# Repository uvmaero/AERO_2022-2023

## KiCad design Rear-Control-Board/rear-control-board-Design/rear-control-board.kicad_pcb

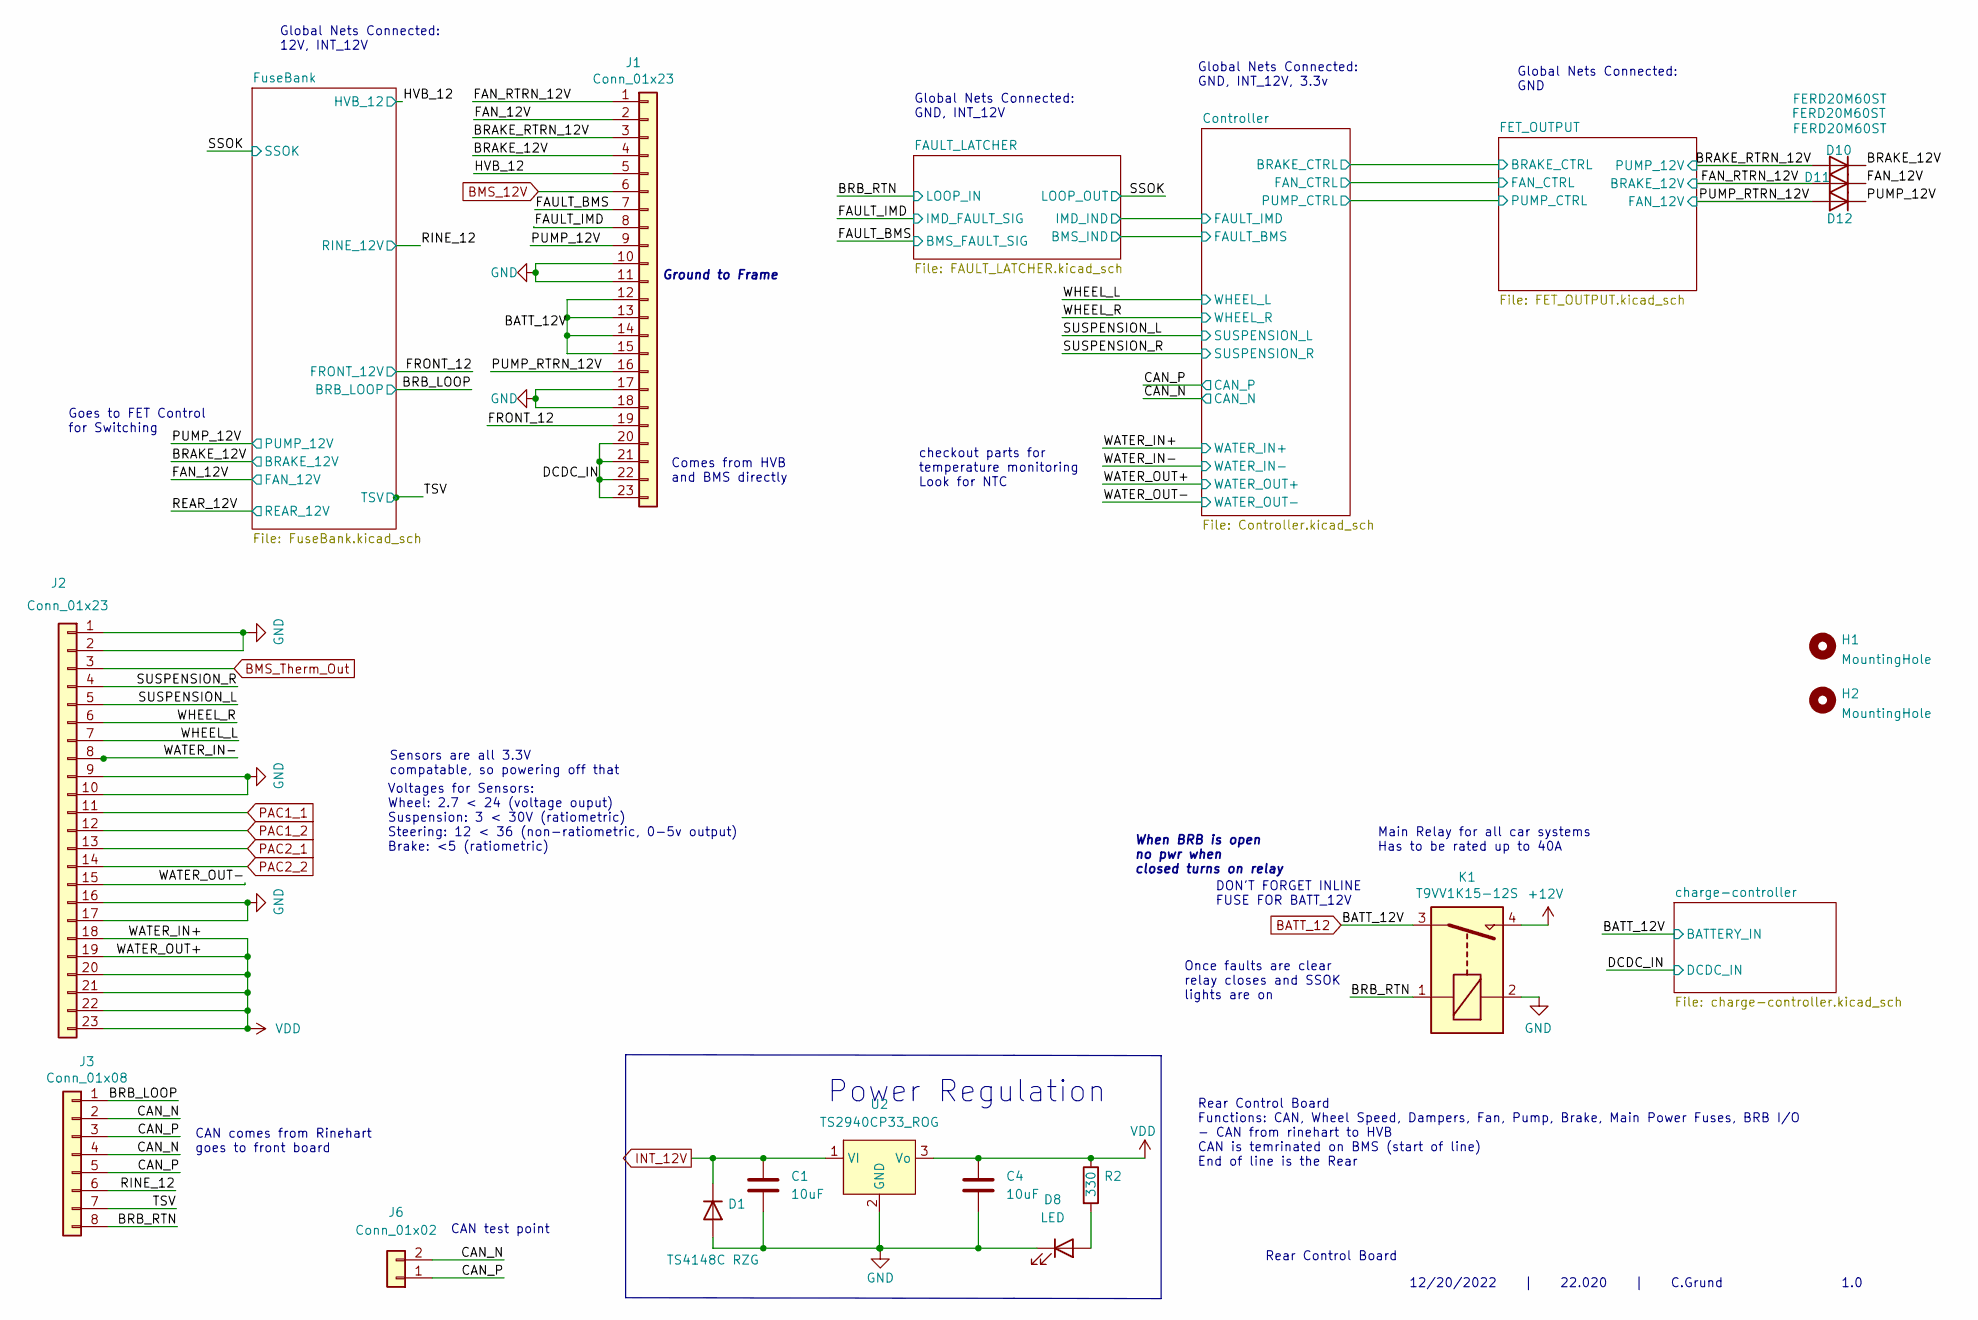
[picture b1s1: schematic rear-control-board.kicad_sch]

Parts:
C1, C4: 10uF; C_0603_1608Metric_Pad1.08x0.95mm_HandSolder
D1: TS4148C RZG; D_0603_1608Metric_Pad1.05x0.95mm_HandSolder
D8: LED; LED_0603_1608Metric_Pad1.05x0.95mm_HandSolder
D10, D11, D12: FERD20M60ST; TO-220-3_Vertical
H1, H2: MountingHole; MountingHole_3.2mm_M3
J1, J2: Conn_01x23; TE_1-770669-1_23pin_Horizontal
J3: Conn_01x08; TE_1-776280-1_8pin_Horizontal
J6: Conn_01x02; JST_NV_B02P-NV_1x02_P5.00mm_Vertical
K1: T9VV1K15-12S; RELAY_T9VV1K15-12S
R2: 330; R_0603_1608Metric_Pad0.98x0.95mm_HandSolder
U2: TS2940CP33_ROG; TO-252-2

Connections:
+12V: K1.4; also elsewhere on the board
/BRAKE_12V: D10.2 (K), J1.4; also elsewhere on the board
/BRAKE_RTRN_12V: D10.1 (A), J1.3; also elsewhere on the board
/BRB_LOOP: J3.1; also elsewhere on the board
/CAN_N: J3.2, J3.4, J6.2; also elsewhere on the board
/CAN_P: J3.3, J3.5, J6.1; also elsewhere on the board
/DCDC_IN: J1.20, J1.21, J1.22, J1.23; also elsewhere on the board
/FAN_12V: D11.2 (K), J1.2; also elsewhere on the board
/FAN_RTRN_12V: D11.1 (A), J1.1; also elsewhere on the board
/FAULT_IMD: J1.8; also elsewhere on the board
/FRONT_12: J1.19; also elsewhere on the board
/HVB_12: J1.5; also elsewhere on the board
/PUMP_12V: D12.2 (K), J1.9; also elsewhere on the board
/PUMP_RTRN_12V: D12.1 (A), J1.16; also elsewhere on the board
/RINE_12: J3.6; also elsewhere on the board
/SUSPENSION_L: J2.5; also elsewhere on the board
/SUSPENSION_R: J2.4; also elsewhere on the board
/TSV: J3.7; also elsewhere on the board
/WATER_IN-: J2.8; also elsewhere on the board
/WATER_OUT-: J2.15; also elsewhere on the board
/WHEEL_L: J2.7; also elsewhere on the board
/WHEEL_R: J2.6; also elsewhere on the board
BATT_12: J1.12, J1.13, J1.14, J1.15, K1.3; also elsewhere on the board
BMS_12V: J1.6; also elsewhere on the board
BMS_Therm_Out: J2.3; also elsewhere on the board
unnamed: D8.2 (A), R2.2
PAC1_1: J2.11; also elsewhere on the board
PAC1_2: J2.12; also elsewhere on the board
PAC2_1: J2.13; also elsewhere on the board
PAC2_2: J2.14; also elsewhere on the board
VDD: C4.1, J2.18, J2.19, J2.20, J2.21, J2.22, J2.23, R2.1, U2.3 (Vo); also elsewhere on the board

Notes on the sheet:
Once faults are clear relay closes and SSOK lights are on
1.0
Comes from HVB and BMS directly
Global Nets Connected: GND
Main Relay for all car systems Has to be rated up to 40A
checkout parts for temperature monitoring Look for NTC
When BRB is open no pwr when closed turns on relay
Global Nets Connected: GND, INT_12V
Voltages for Sensors: Wheel: 2.7 < 24 (voltage ouput) Suspension: 3 < 30V (ratiometric) Steering: 12 < 36 (non-ratiometric, 0-5v output) Brake: <5 (ratiometric)
DON'T FORGET INLINE FUSE FOR BATT_12V
CAN test point
12/20/2022 | 22.020 | C.Grund
Rear Control Board Functions: CAN, Wheel Speed, Dampers, Fan, Pump, Brake, Main Power Fuses, BRB I/O - CAN from rinehart to HVB CAN is temrinated on BMS (start of line) End of line is the Rear
Goes to FET Control for Switching
Ground to Frame
CAN comes from Rinehart goes to front board
Power Regulation
Global Nets Connected: GND, INT_12V, 3.3v
Sensors are all 3.3V compatable, so powering off that
Global Nets Connected: 12V, INT_12V
Rear Control Board

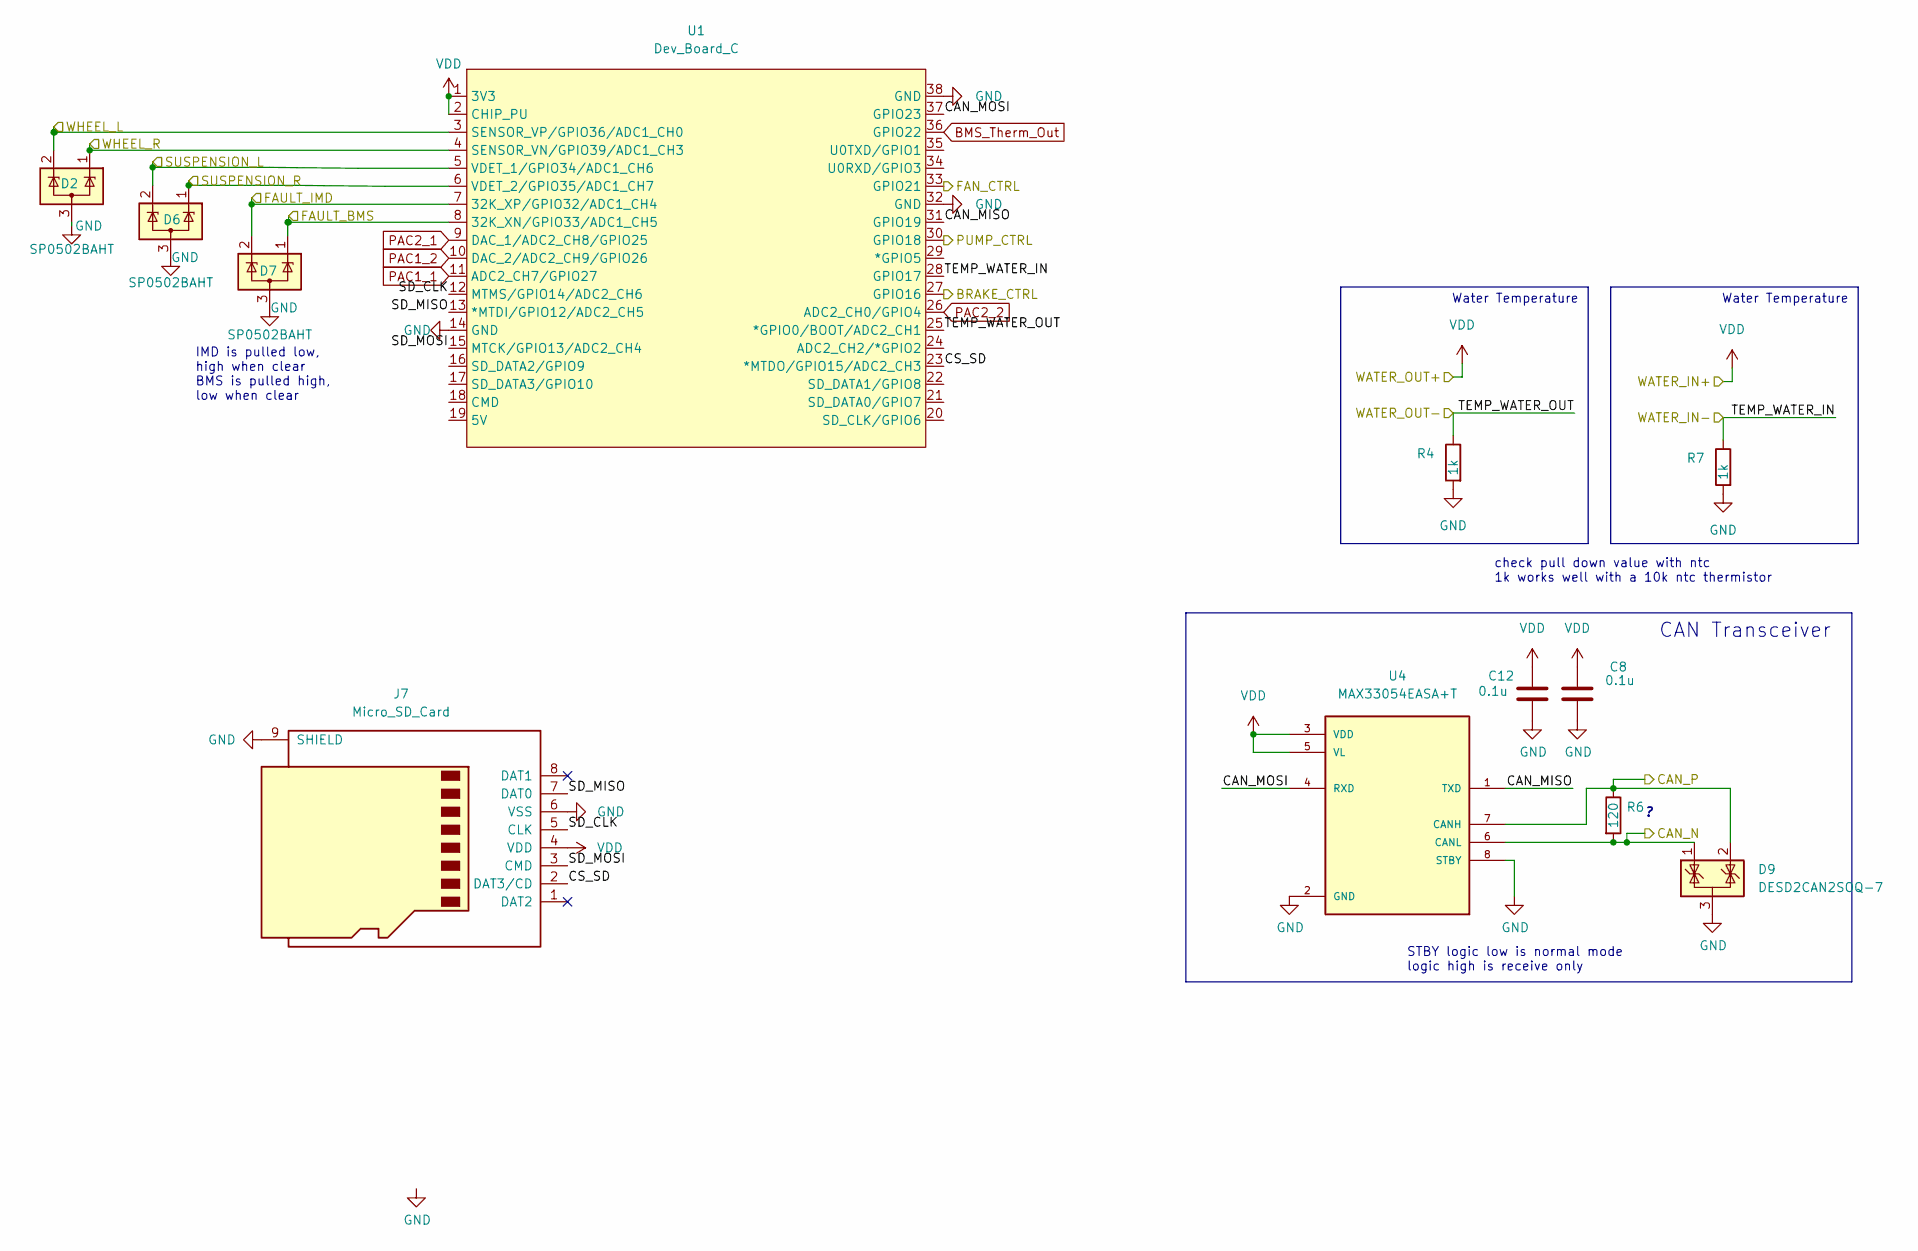
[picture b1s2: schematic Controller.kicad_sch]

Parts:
C8, C12: 0.1u; C_0603_1608Metric_Pad1.08x0.95mm_HandSolder
D2, D6, D7: SP0502BAHT; SOT-23
D9: DESD2CAN2SOQ-7; SOT-23
J7: Micro_SD_Card; microSD_HC_Wuerth_693072010801
R4, R7: 1k; R_0603_1608Metric_Pad0.98x0.95mm_HandSolder
R6: 120; R_0603_1608Metric_Pad0.98x0.95mm_HandSolder
U1: Dev_Board_C; ESP32-DevKitC
U4: MAX33054EASA+T; SOIC127P600X175-8N

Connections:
/CAN_N: D9.1 (K), R6.2, U4.6 (CANL); also elsewhere on the board
/CAN_P: D9.2 (K), R6.1, U4.7 (CANH); also elsewhere on the board
/Controller/BRAKE_CTRL: U1.27 (GPIO16); also elsewhere on the board
/Controller/CAN_MISO: U1.31 (GPIO19), U4.1 (TXD)
/Controller/CAN_MOSI: U1.37 (GPIO23), U4.4 (RXD)
/Controller/CS_SD: J7.2 (DAT3/CD), U1.23 (*MTDO/GPIO15/ADC2_CH3)
/Controller/FAN_CTRL: U1.33 (GPIO21); also elsewhere on the board
/Controller/FAULT_IMD: D7.2 (K), U1.7 (32K_XP/GPIO32/ADC1_CH4); also elsewhere on the board
/Controller/PUMP_CTRL: U1.30 (GPIO18); also elsewhere on the board
/Controller/SD_CLK: J7.5 (CLK), U1.12 (MTMS/GPIO14/ADC2_CH6)
/Controller/SD_MISO: J7.7 (DAT0), U1.13 (*MTDI/GPIO12/ADC2_CH5)
/Controller/SD_MOSI: J7.3 (CMD), U1.15 (MTCK/GPIO13/ADC2_CH4)
/SUSPENSION_L: D6.2 (K), U1.5 (VDET_1/GPIO34/ADC1_CH6); also elsewhere on the board
/SUSPENSION_R: D6.1 (K), U1.6 (VDET_2/GPIO35/ADC1_CH7); also elsewhere on the board
/WATER_IN-: R7.1, U1.28 (GPIO17); also elsewhere on the board
/WATER_OUT-: R4.1, U1.25 (*GPIO0/BOOT/ADC2_CH1); also elsewhere on the board
/WHEEL_L: D2.2 (K), U1.3 (SENSOR_VP/GPIO36/ADC1_CH0); also elsewhere on the board
/WHEEL_R: D2.1 (K), U1.4 (SENSOR_VN/GPIO39/ADC1_CH3); also elsewhere on the board
BMS_Therm_Out: U1.36 (GPIO22); also elsewhere on the board
PAC1_1: U1.11 (ADC2_CH7/GPIO27); also elsewhere on the board
PAC1_2: U1.10 (DAC_2/ADC2_CH9/GPIO26); also elsewhere on the board
PAC2_1: U1.9 (DAC_1/ADC2_CH8/GPIO25); also elsewhere on the board
PAC2_2: U1.26 (ADC2_CH0/GPIO4); also elsewhere on the board
VDD: C8.1, C12.1, J7.4 (VDD), U1.1 (3V3), U1.2 (CHIP_PU), U4.3 (VDD), U4.5 (VL); also elsewhere on the board

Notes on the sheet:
Water Temperature
check pull down value with ntc 1k works well with a 10k ntc thermistor
CAN Transceiver
IMD is pulled low, high when clear BMS is pulled high, low when clear
STBY logic low is normal mode logic high is receive only

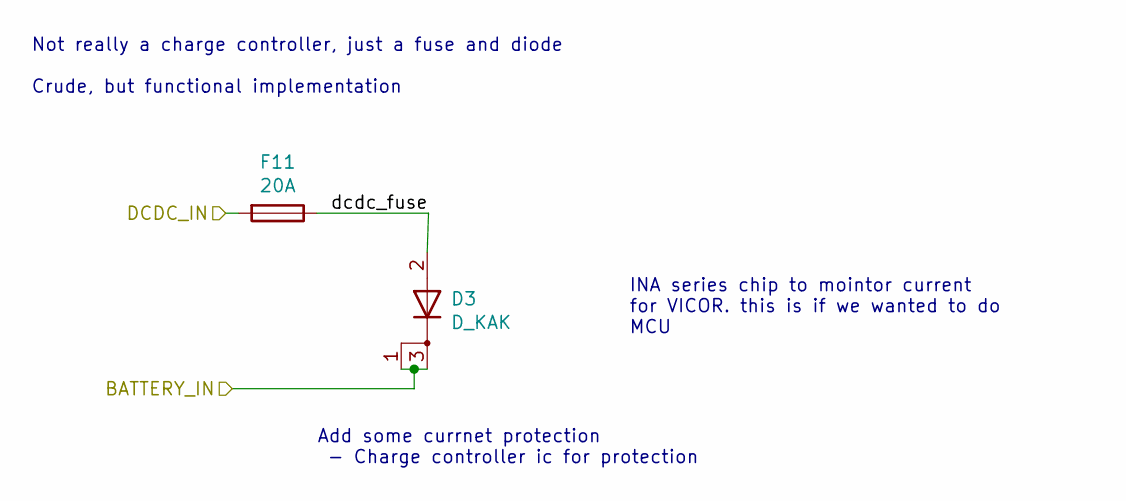
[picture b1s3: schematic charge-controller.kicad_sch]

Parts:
D3: D_KAK; TO-252-2
F11: 20A; Fuseholder_Blade_Mini_Keystone_3568

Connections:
/DCDC_IN: F11.2; also elsewhere on the board
/charge-controller/dcdc_fuse: D3.2 (A), F11.1
BATT_12: D3.1 (K), D3.3 (K); also elsewhere on the board

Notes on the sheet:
Add some currnet protection - Charge controller ic for protection
Not really a charge controller, just a fuse and diode Crude, but functional implementation
INA series chip to mointor current for VICOR. this is if we wanted to do MCU

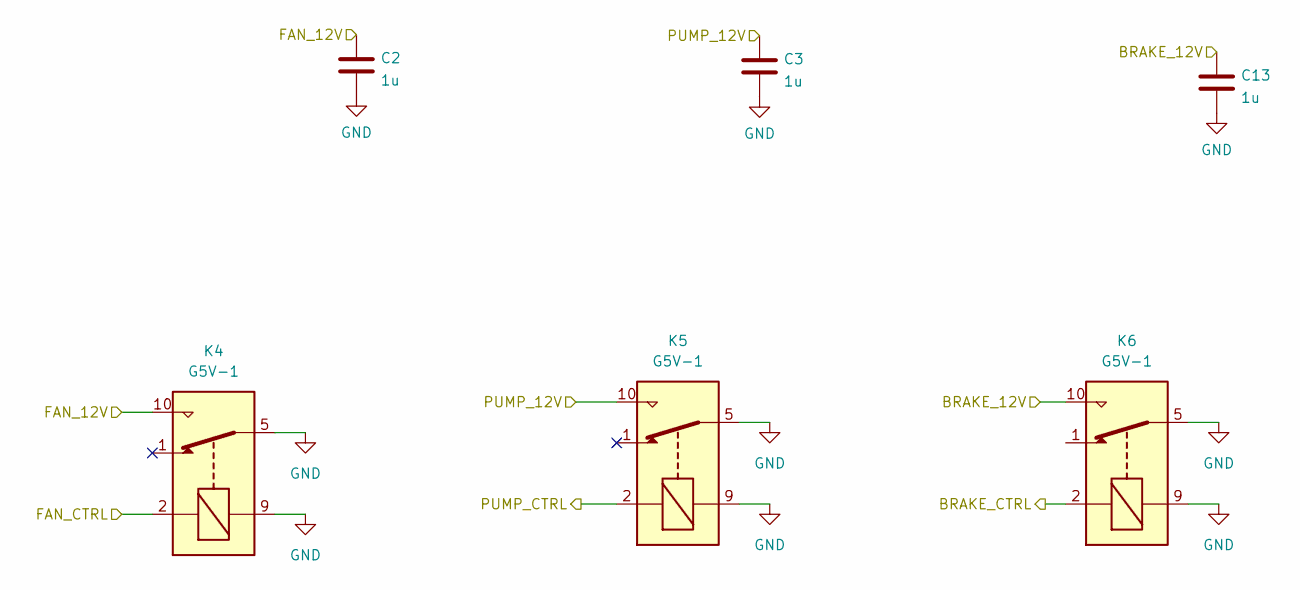
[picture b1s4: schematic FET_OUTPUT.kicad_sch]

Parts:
C2, C3, C13: 1u; C_0603_1608Metric_Pad1.08x0.95mm_HandSolder
K4, K5, K6: G5V-1; Relay_SPDT_Omron_G5V-1

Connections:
/BRAKE_RTRN_12V: C3.1, K5.10; also elsewhere on the board
/Controller/BRAKE_CTRL: K6.2; also elsewhere on the board
/Controller/FAN_CTRL: K4.2; also elsewhere on the board
/Controller/PUMP_CTRL: K5.2; also elsewhere on the board
/FAN_RTRN_12V: C13.1, K6.10; also elsewhere on the board
/PUMP_RTRN_12V: C2.1, K4.10; also elsewhere on the board

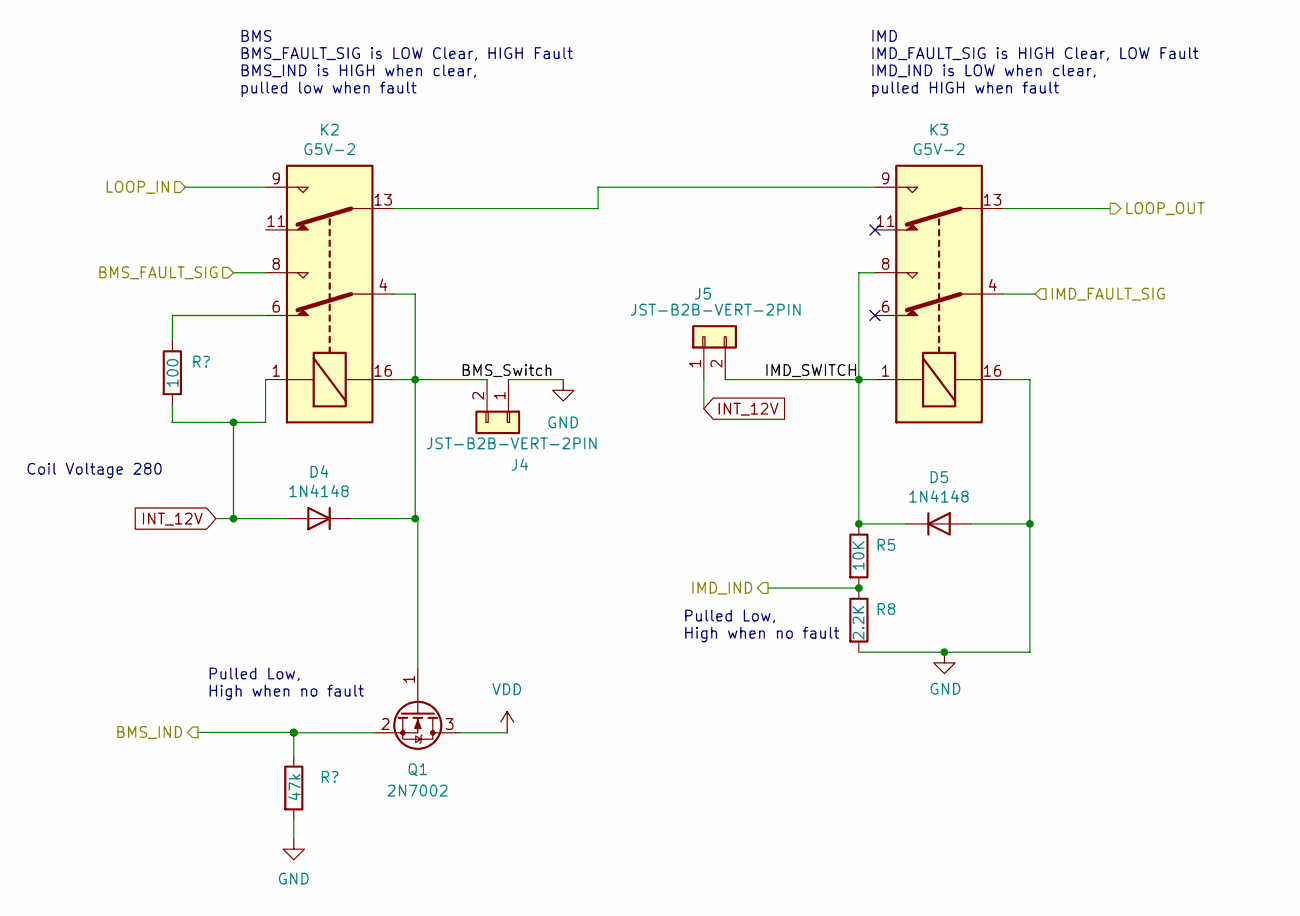
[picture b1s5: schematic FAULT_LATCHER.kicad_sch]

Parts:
D4, D5: 1N4148; D_SOD-123
J4, J5: JST-B2B-VERT-2PIN; JST_XH_B2B-XH-AM_1x02_P2.50mm_Vertical
K2, K3: G5V-2; Relay_DPDT_Omron_G5V-2
Q1: 2N7002; SOT-23
R5: 10K; R_0603_1608Metric_Pad0.98x0.95mm_HandSolder
R8: 2.2K; R_0603_1608Metric_Pad0.98x0.95mm_HandSolder

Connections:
/Controller/FAULT_IMD: R5.2, R8.1; also elsewhere on the board
/FAULT_IMD: K3.4; also elsewhere on the board
/FAULT_LATCHER/IMD_SWITCH: D5.1 (K), J5.2, K3.1, K3.8, R5.1
/SSOK: K3.13; also elsewhere on the board
unnamed 39: Q1.3 (D); also elsewhere on the board

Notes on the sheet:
Coil Voltage 280
IMD IMD_FAULT_SIG is HIGH Clear, LOW Fault IMD_IND is LOW when clear, pulled HIGH when fault
Pulled Low, High when no fault
BMS BMS_FAULT_SIG is LOW Clear, HIGH Fault BMS_IND is HIGH when clear, pulled low when fault

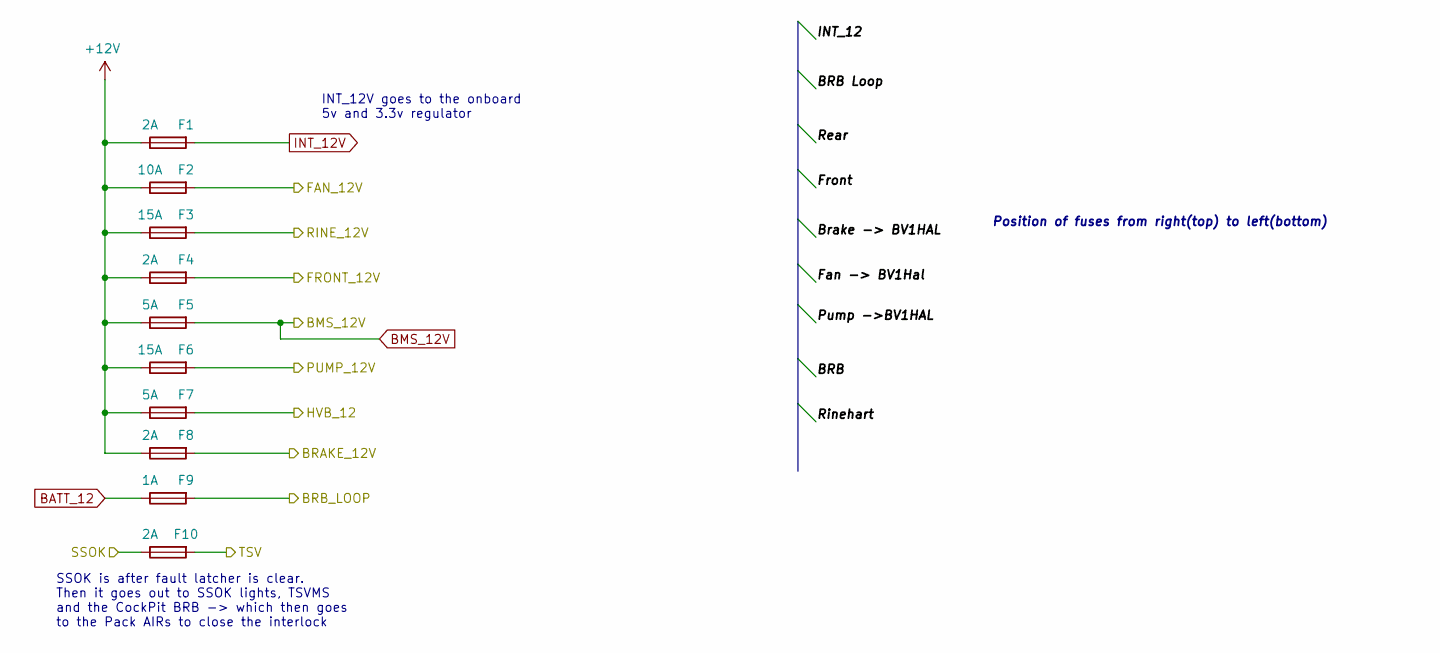
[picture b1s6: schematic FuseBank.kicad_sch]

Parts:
F1, F4, F8, F10: 2A; Fuseholder_Blade_Mini_Keystone_3568
F2: 10A; Fuseholder_Blade_Mini_Keystone_3568
F3, F6: 15A; Fuseholder_Blade_Mini_Keystone_3568
F5, F7: 5A; Fuseholder_Blade_Mini_Keystone_3568
F9: 1A; Fuseholder_Blade_Mini_Keystone_3568

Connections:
+12V: F1.1, F2.1, F3.1, F4.1, F5.1, F6.1, F7.1, F8.1; also elsewhere on the board
/BRAKE_12V: F8.2; also elsewhere on the board
/BRB_LOOP: F9.2; also elsewhere on the board
/FAN_12V: F2.2; also elsewhere on the board
/FRONT_12: F4.2; also elsewhere on the board
/HVB_12: F7.2; also elsewhere on the board
/PUMP_12V: F6.2; also elsewhere on the board
/RINE_12: F3.2; also elsewhere on the board
/SSOK: F10.1; also elsewhere on the board
/TSV: F10.2; also elsewhere on the board
BATT_12: F9.1; also elsewhere on the board
BMS_12V: F5.2; also elsewhere on the board

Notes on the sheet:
SSOK is after fault latcher is clear. Then it goes out to SSOK lights, TSVMS and the CockPit BRB -> which then goes to the Pack AIRs to close the interlock
Position of fuses from right(top) to left(bottom)
INT_12V goes to the onboard 5v and 3.3v regulator

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
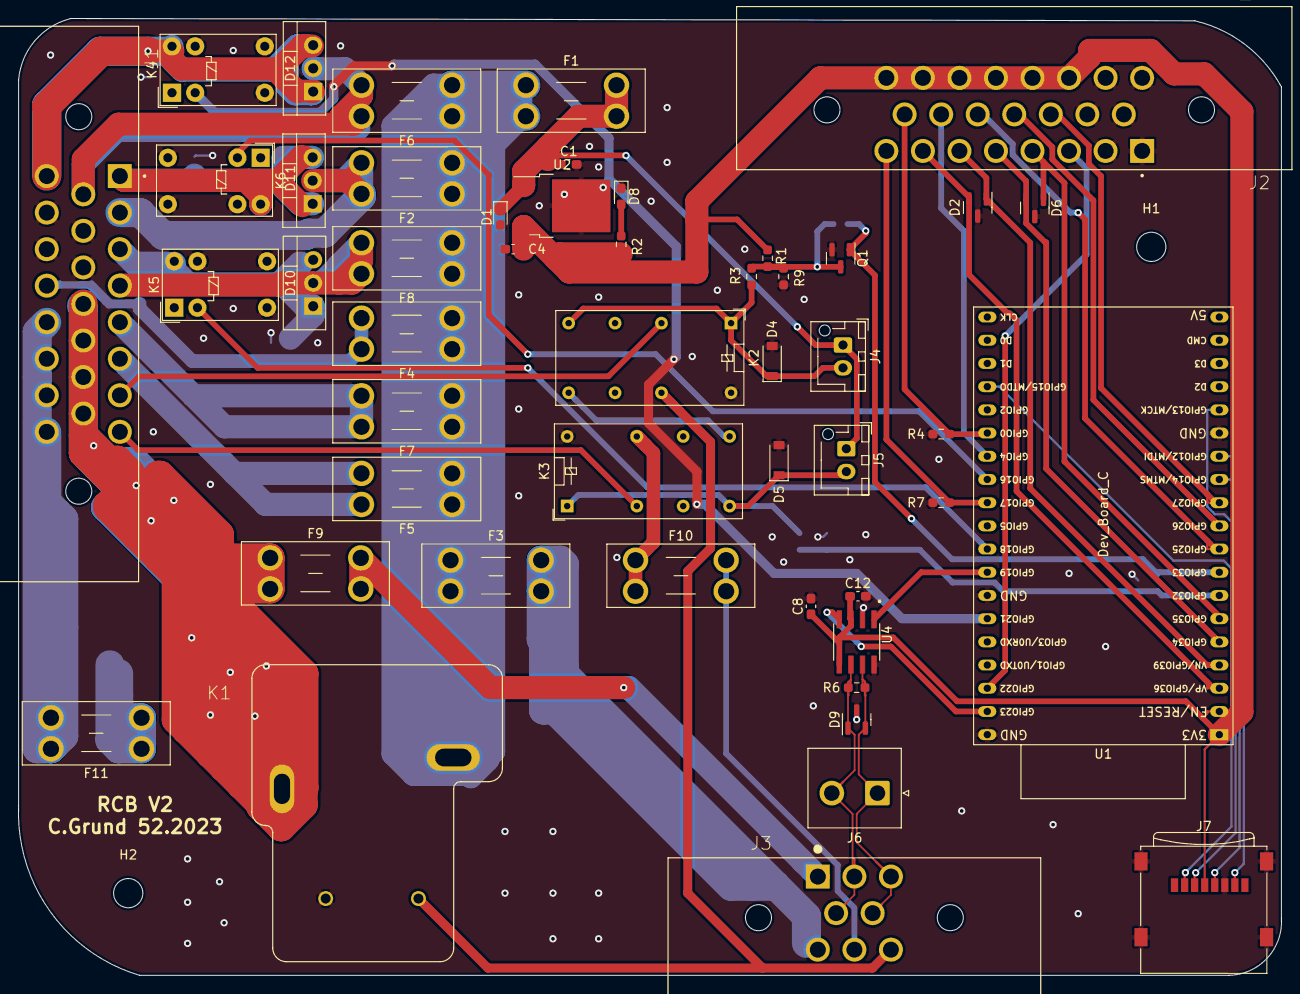
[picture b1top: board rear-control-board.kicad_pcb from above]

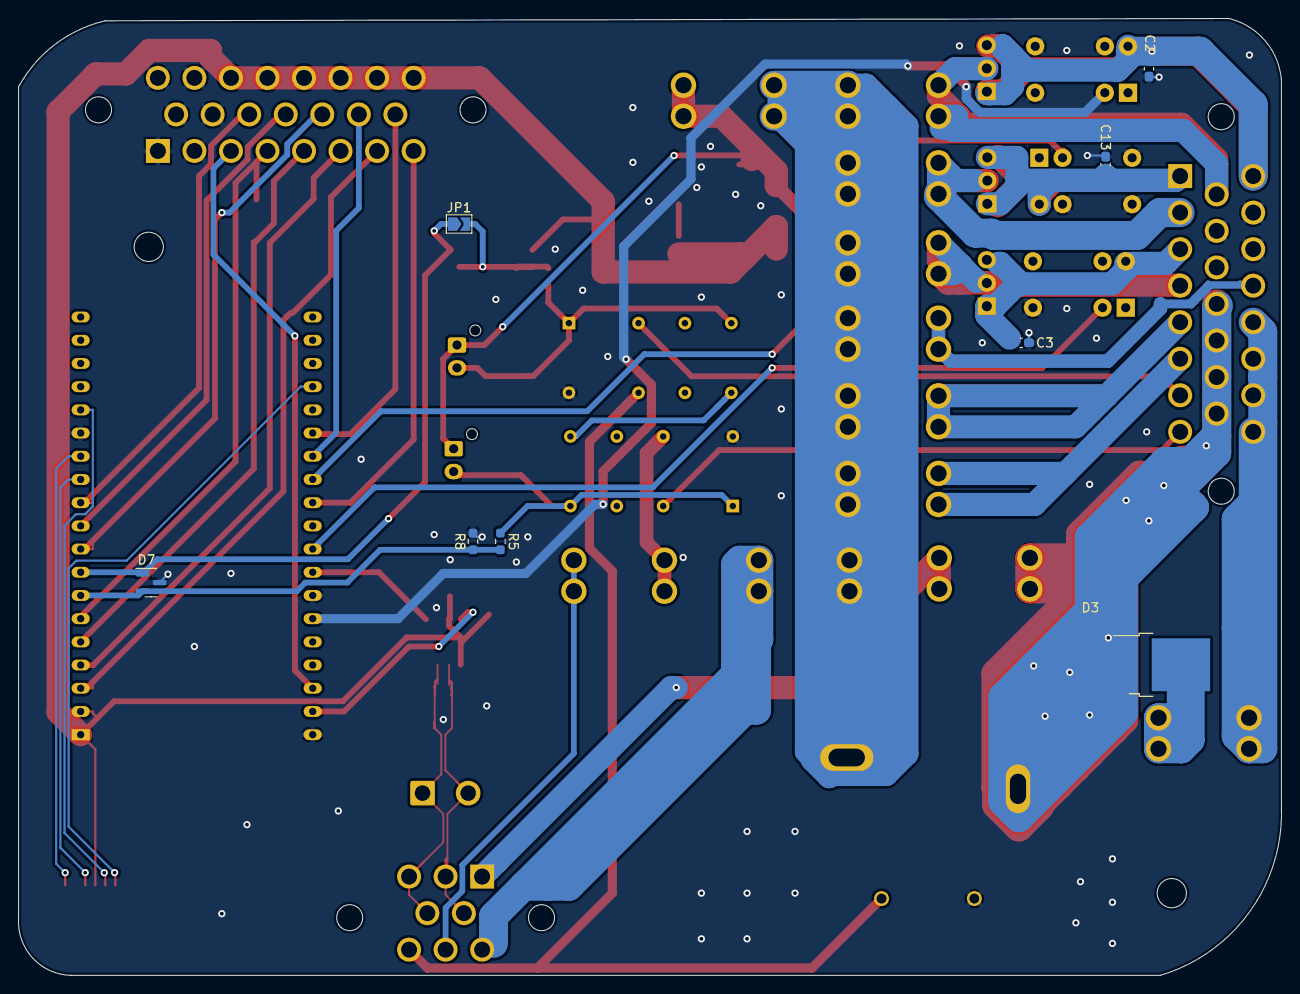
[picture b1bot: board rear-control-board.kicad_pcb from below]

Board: 2 copper layers, 138.3 x 104.8 mm, 59 parts (8 on the bottom side), 52 nets.

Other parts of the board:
JP1: SolderJumper_2_Open; SolderJumper-2_P1.3mm_Open_TrianglePad1.0x1.5mm
R1: 100k; R_0603_1608Metric_Pad0.98x0.95mm_HandSolder
R3: 10K; R_0603_1608Metric_Pad0.98x0.95mm_HandSolder
R9: 2.2K; R_0603_1608Metric_Pad0.98x0.95mm_HandSolder

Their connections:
unnamed 39: JP1.2 (B), R1.2, R3.2, R9.1; also elsewhere on the board
VDD: R1.1; also elsewhere on the board

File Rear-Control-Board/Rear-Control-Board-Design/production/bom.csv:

Designator,Footprint,Quantity,Value,LCSC Part #
C1,0603,1,10uF,
C12,0603,1,0.1u,
C13,0603,1,1u,
C2,0603,1,1u,
C3,0603,1,1u,
C4,0603,1,10uF,
C8,0603,1,0.1u,
D1,0603,1,TS4148C RZG,
"D10, D11, D12",TO-220-3_Vertical,3,FERD20M60ST,
"D2, D6, D7",SOT-23,3,SP0502BAHT,
D3,TO-252-2,1,D_KAK,
"D4, D5",D_SOD-123,2,1N4148,
D8,0603,1,LED,
D9,SOT-23,1,DESD2CAN2SOQ-7,
"F1, F10, F4, F8",Fuseholder_Blade_Mini_Keystone_3568,4,2A,
F11,Fuseholder_Blade_Mini_Keystone_3568,1,20A,
F2,Fuseholder_Blade_Mini_Keystone_3568,1,10A,
"F3, F6",Fuseholder_Blade_Mini_Keystone_3568,2,15A,
"F5, F7",Fuseholder_Blade_Mini_Keystone_3568,2,5A,
F9,Fuseholder_Blade_Mini_Keystone_3568,1,1A,
"H1, H2",MountingHole_3.2mm_M3,2,MountingHole,
"J1, J2",TE_1-770669-1_23pin_Horizontal,2,Conn_01x23,
J3,TE_1-776280-1_8pin_Horizontal,1,Conn_01x08,
"J4, J5",JST_XH_B2B-XH-AM_1x02_P2.50mm_Vertical,2,JST-B2B-VERT-2PIN,
J6,JST_NV_B02P-NV_1x02_P5.00mm_Vertical,1,Conn_01x02,
J7,microSD_HC_Wuerth_693072010801,1,Micro_SD_Card,
JP1,SolderJumper-2_P1.3mm_Open_TrianglePad1.0x1.5mm,1,SolderJumper_2_Open,
K1,RELAY_T9VV1K15-12S,1,T9VV1K15-12S,
"K2, K3",Relay_DPDT_Omron_G5V-2,2,G5V-2,
"K4, K5, K6",Relay_SPDT_Omron_G5V-1,3,G5V-1,
Q1,SOT-23,1,2N7002,
R1,0603,1,100k,
R2,0603,1,330,
R3,0603,1,10K,
R4,0603,1,1k,
R5,0603,1,10K,
R6,0603,1,120,
R7,0603,1,1k,
R8,0603,1,2.2K,
R9,0603,1,2.2K,
U1,ESP32-DevKitC,1,Dev_Board_C,
U2,TO-252-2,1,TS2940CP33_ROG,
U4,SOIC127P600X175-8N,1,MAX33054EASA+T,

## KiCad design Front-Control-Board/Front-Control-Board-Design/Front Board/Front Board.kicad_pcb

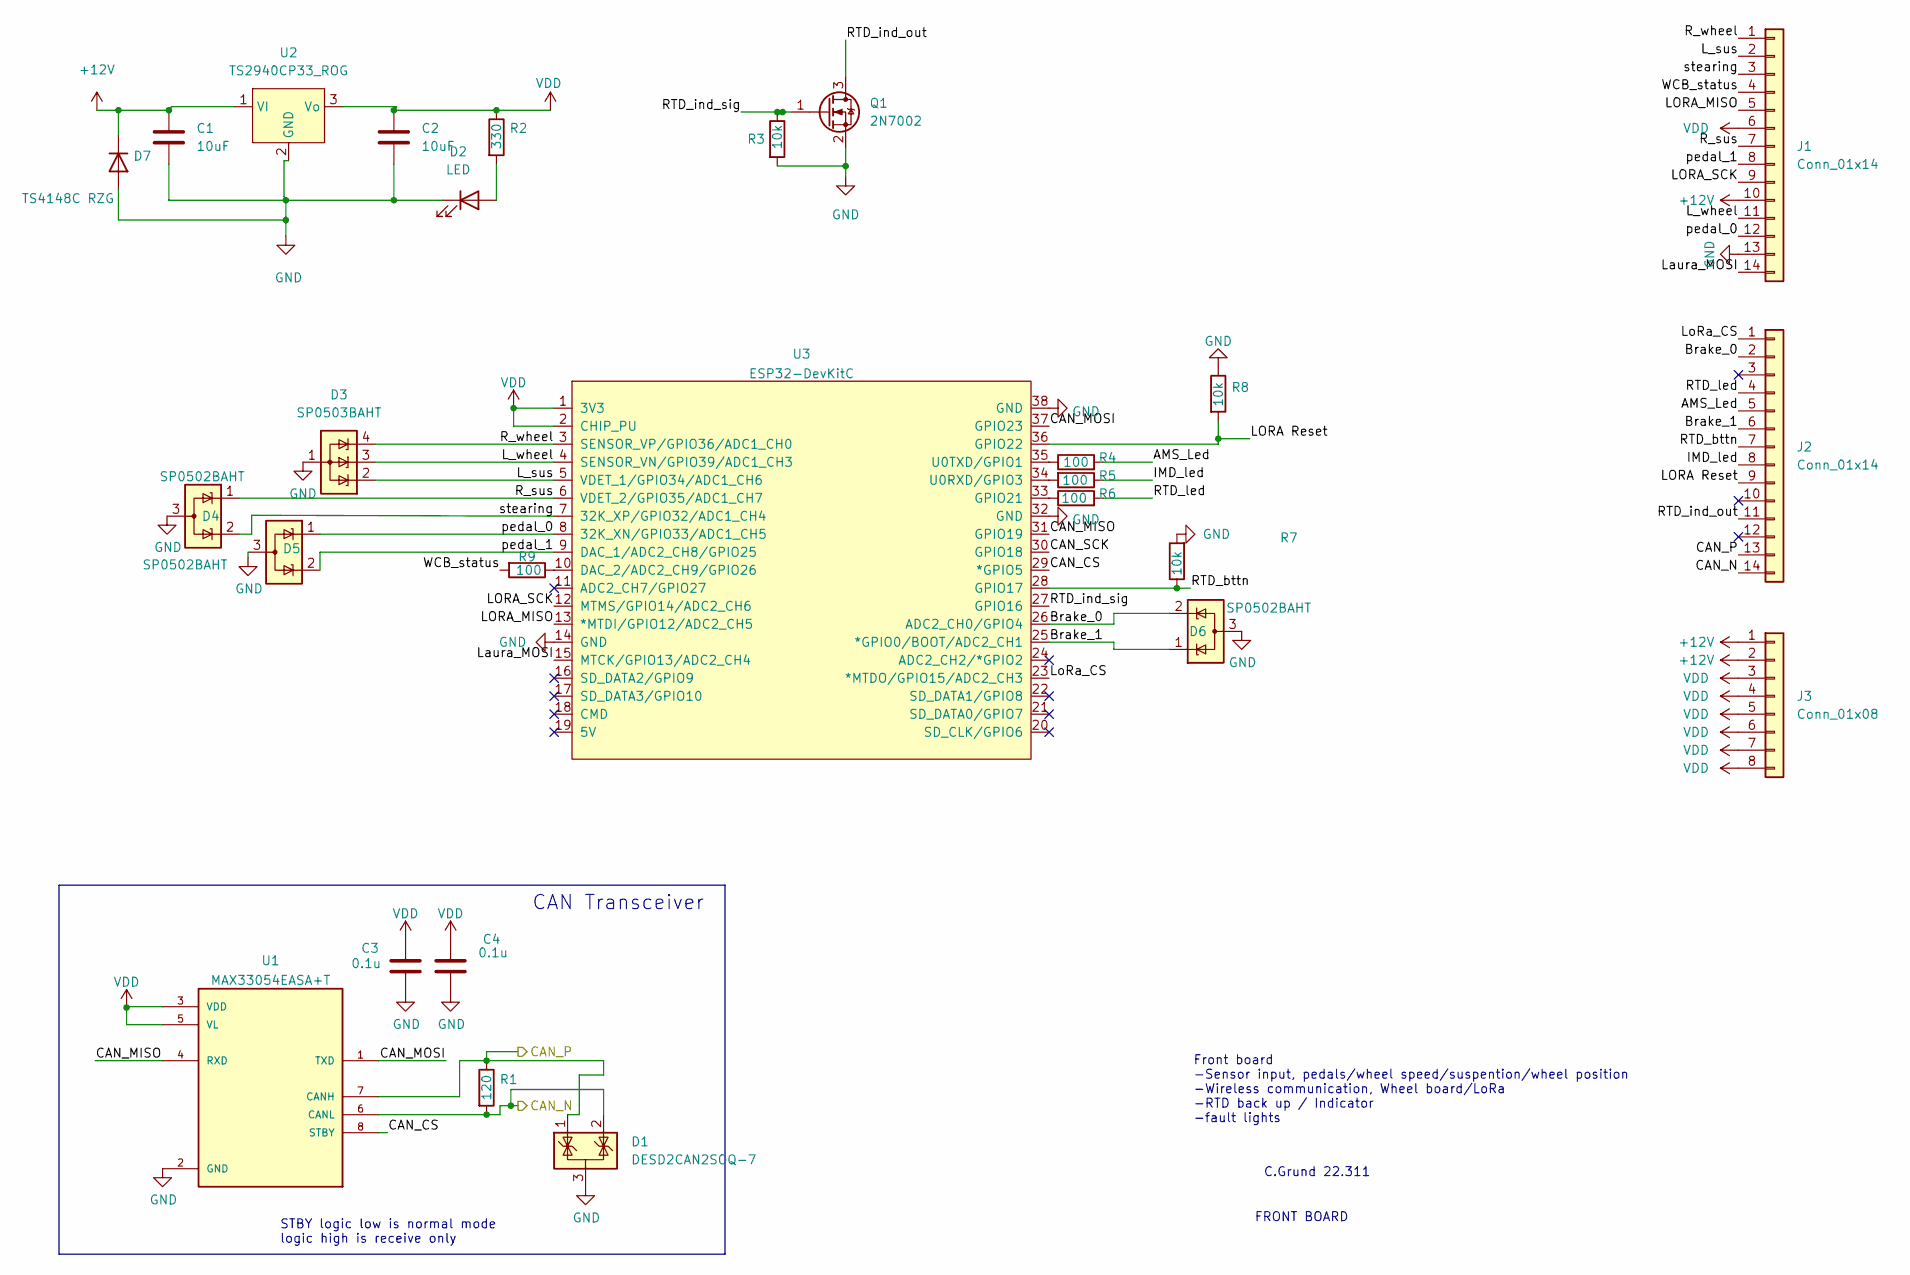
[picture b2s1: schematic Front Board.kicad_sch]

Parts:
C1, C2: 10uF; C_0603_1608Metric_Pad1.08x0.95mm_HandSolder
C3, C4: 0.1u; C_0603_1608Metric_Pad1.08x0.95mm_HandSolder
D1: DESD2CAN2SOQ-7; SOT-23
D2: LED; LED_0603_1608Metric_Pad1.05x0.95mm_HandSolder
D3: SP0503BAHT; SOT-143
D4, D5, D6: SP0502BAHT; SOT-23
D7: TS4148C RZG; D_0603_1608Metric_Pad1.05x0.95mm_HandSolder
J1, J2: Conn_01x14; TE_1-776266-1_14pin_Horizontal
J3: Conn_01x08; TE_1-776280-1_8pin_Horizontal
Q1: 2N7002; SOT-23
R1: 120; R_0603_1608Metric_Pad0.98x0.95mm_HandSolder
R2: 330; R_0603_1608Metric_Pad0.98x0.95mm_HandSolder
R3, R7, R8: 10k; R_0603_1608Metric_Pad0.98x0.95mm_HandSolder
R4, R5, R6, R9: 100; R_0603_1608Metric_Pad0.98x0.95mm_HandSolder
U1: MAX33054EASA+T; SOIC127P600X175-8N
U2: TS2940CP33_ROG; TO-252-2
U3: ESP32-DevKitC

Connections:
+12V: C1.1, D7.1 (K), J1.10, J3.1, J3.2, U2.1 (VI)
/AMS_Led: J2.5, R4.2
/Brake_0: D6.2 (K), J2.2, U3.26 (ADC2_CH0/GPIO4)
/Brake_1: D6.1 (K), J2.6, U3.25 (*GPIO0/BOOT/ADC2_CH1)
/CAN_CS: U1.8 (STBY), U3.29 (*GPIO5)
/CAN_MISO: U1.4 (RXD), U3.31 (GPIO19)
/CAN_MOSI: U1.1 (TXD), U3.37 (GPIO23)
/CAN_N: D1.2 (K), J2.14, R1.2, U1.6 (CANL)
/CAN_P: D1.1 (K), J2.13, R1.1, U1.7 (CANH)
/CAN_SCK: U3.30 (GPIO18)
/IMD_led: J2.8, R5.1
/LORA Reset: J2.9, R8.2, U3.36 (GPIO22)
/LORA_MISO: J1.5, U3.13 (*MTDI/GPIO12/ADC2_CH5)
/LORA_SCK: J1.9, U3.12 (MTMS/GPIO14/ADC2_CH6)
/L_sus: D3.2 (K), J1.2, U3.5 (VDET_1/GPIO34/ADC1_CH6)
/L_wheel: D3.3 (K), J1.11, U3.4 (SENSOR_VN/GPIO39/ADC1_CH3)
/Laura_MOSI: J1.14, U3.15 (MTCK/GPIO13/ADC2_CH4)
/LoRa_CS: J2.1, U3.23 (*MTDO/GPIO15/ADC2_CH3)
/RTD_bttn: J2.7, R7.1, U3.28 (GPIO17)
/RTD_ind_out: J2.11, Q1.3 (D)
/RTD_ind_sig: Q1.1 (G), R3.1, U3.27 (GPIO16)
/RTD_led: J2.4, R6.2
/R_sus: D4.1 (K), J1.7, U3.6 (VDET_2/GPIO35/ADC1_CH7)
/R_wheel: D3.4 (K), J1.1, U3.3 (SENSOR_VP/GPIO36/ADC1_CH0)
/WCB_status: J1.4, R9.2
/pedal_0: D5.1 (K), J1.12, U3.8 (32K_XN/GPIO33/ADC1_CH5)
/pedal_1: D5.2 (K), J1.8, U3.9 (DAC_1/ADC2_CH8/GPIO25)
/stearing: D4.2 (K), J1.3, U3.7 (32K_XP/GPIO32/ADC1_CH4)
GND: C1.2, C2.2, C3.2, C4.2, D1.3 (A), D2.1 (K), D3.1 (A), D4.3 (A), D5.3 (A), D6.3 (A), D7.2 (A), J1.13, Q1.2 (S), R3.2, R7.2, R8.1, U1.2 (GND), U2.2 (GND), U3.14 (GND), U3.32 (GND), U3.38 (GND)
unnamed: D2.2 (A), R2.2
unnamed: R4.1, U3.35 (U0TXD/GPIO1)
unnamed: R5.2, U3.34 (U0RXD/GPIO3)
unnamed: R6.1, U3.33 (GPIO21)
unnamed: R9.1, U3.10 (DAC_2/ADC2_CH9/GPIO26)
VDD: C2.1, C3.1, C4.1, J1.6, J3.3, J3.4, J3.5, J3.6, J3.7, J3.8, R2.1, U1.3 (VDD), U1.5 (VL), U2.3 (Vo), U3.1 (3V3), U3.2 (CHIP_PU)

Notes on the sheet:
CAN Transceiver
FRONT BOARD
C.Grund 22.311
Front board -Sensor input, pedals/wheel speed/suspention/wheel position -Wireless communication, Wheel board/LoRa -RTD back up / Indicator -fault lights
STBY logic low is normal mode logic high is receive only
